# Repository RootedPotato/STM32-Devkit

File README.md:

# STM32G474CCTX Devkit

## What is it?
This is small devkit(development board) with 40 pins(2X20 Pins).
## Why I made it?
I made its for serval thinks:
- To get more knowledge about devkits
- I needed more ADC inputs than Black Pill
- Preciser PWM outputs 
- Small size factor

## Hardware
I will not name all components or all feutures with, which you can experment, but some of most important:
- Mcu: STM32G474CCTX
- Clock: 16Mhz outside clock with 2 decompling capacitors
- LDO: Its have AMS1117-3.3v, but I think that you can use others if the same footprint and same A and V
- SWO/USB: Its have SWO debuging and Micro USB B

## Pinout
### Connector J3(Left)
1. Power +3.3V
2. Power GND
3. Power VBUS
4. PC13 - TIM/GPIO
5. PC14 - GPIO
6. PC15 - GPIO
7. PA0 - ADC/TIM
8. PA1 - ADC/TIM
9. PA2 - ADC/TIM
10. PA3 - ADC/TIM
11. PA4 - ADC/TIM/SPI1
12. PA5 - ADC/TIM/SPI1
13. PA6 - ADC/TIM/SPI1
14. PA7 - ADC/TIM/SPI1
15. PB0 - ADC/TIM
16. PB1 - ADC/TIM
17. PB2 - ADC/TIM
18. PA14 - SWCLK
19. PB3 - SWO
20. PA13 - SWDIO
### Connector J6(Right)
1. Power +3.3V
2. Power GND
3. Power +5V
4. PB9 - TIM/GPIO
5. PB7 - TIM/GPIO
6. PB6 - TIM/GPIO
7. PB5 - TIM/GPIO
8. PB4 - TIM/GPIO
9. PA15 - ADC/TIM
10. PA10 - TIM/GPIO
11. PA9 - ADC/TIM
12. PA8 - ADC/TIM
13. PB15 - ADC/TIM
14. PB14 - ADC/TIM
15. PB13 - ADC/GPIO
16. PB12 - ADC/GPIO
17. PB11 - ADC/TIM
18. PB10 - TIM/GPIO
19. Power GND
20. Power +3.3V
## License
Its open source with MIT license.

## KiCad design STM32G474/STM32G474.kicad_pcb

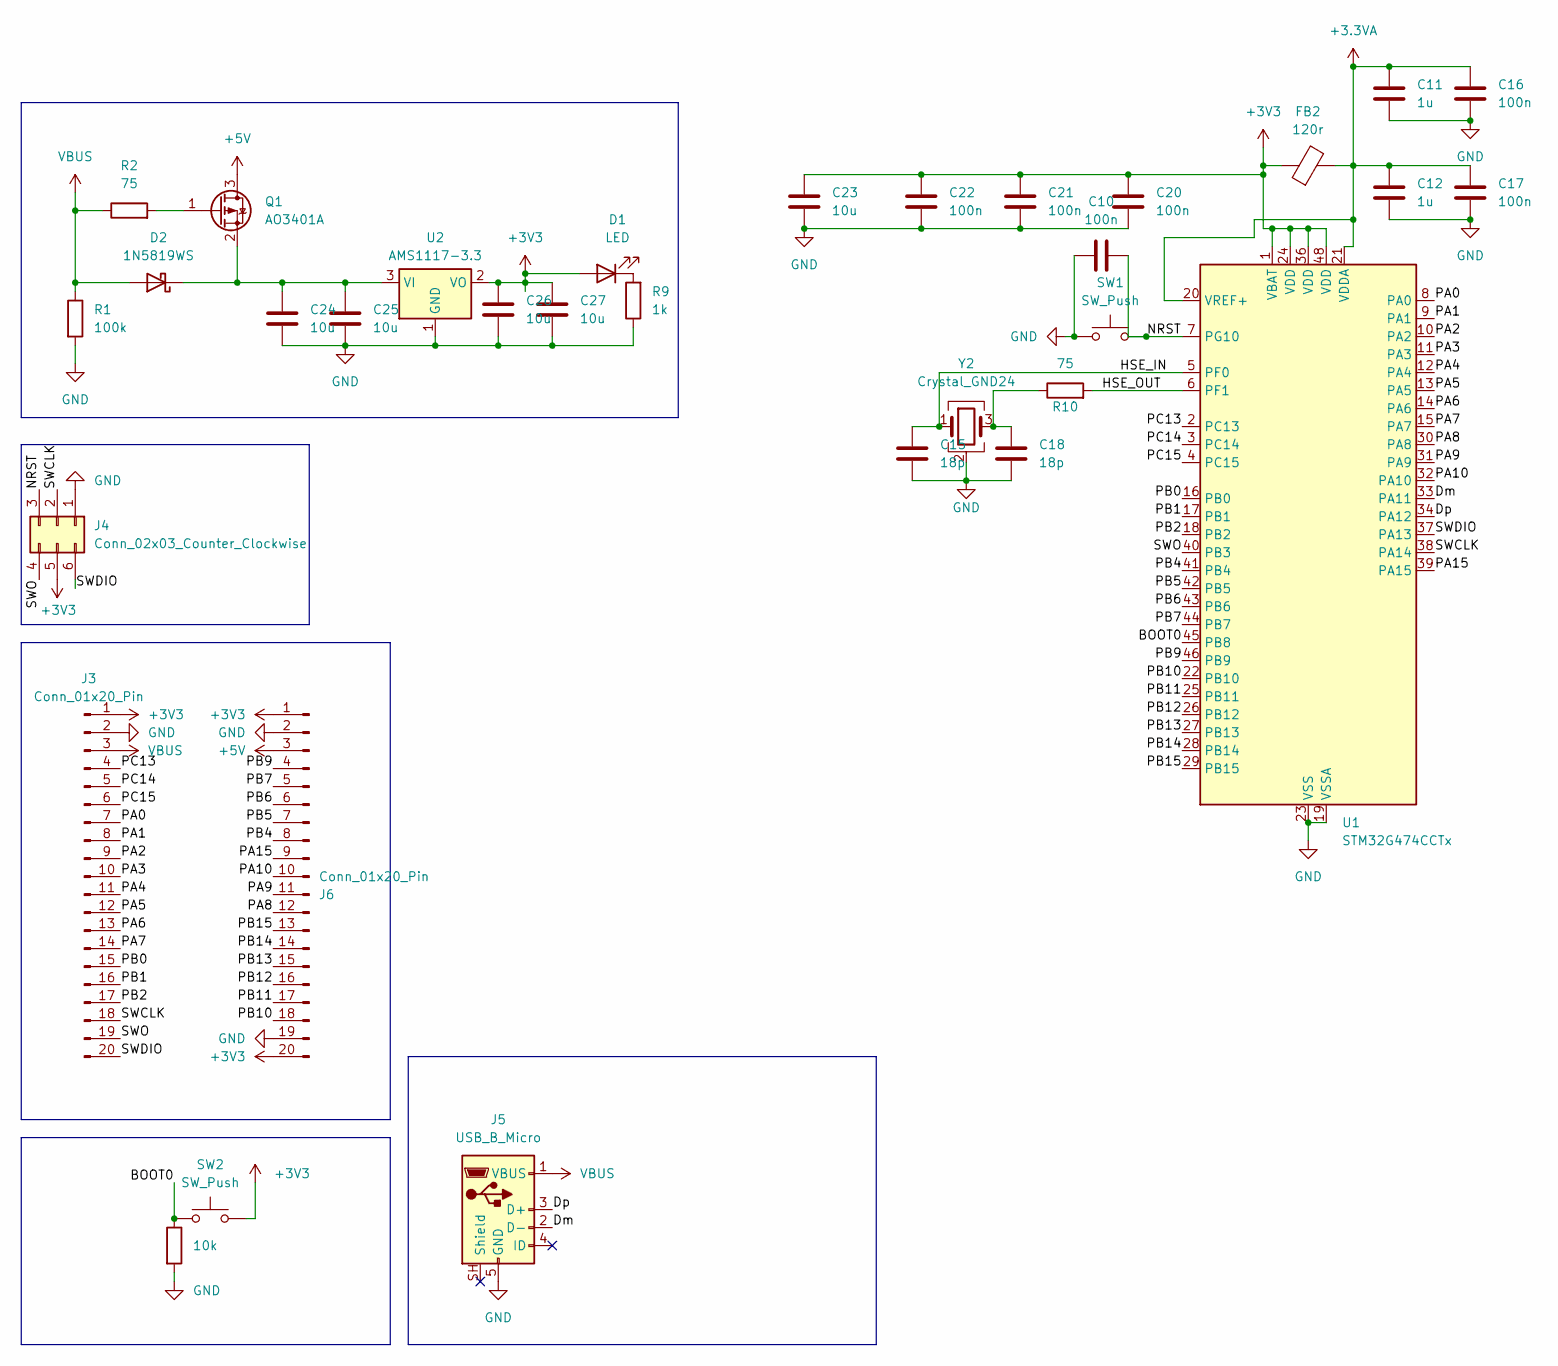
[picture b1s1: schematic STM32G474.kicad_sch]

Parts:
C10, C16, C17, C20, C21, C22: 100n; C_0805_2012Metric_Pad1.18x1.45mm_HandSolder; LCSC C49678
C11, C12: 1u; C_0805_2012Metric_Pad1.18x1.45mm_HandSolder; LCSC C15849
C15, C18: 18p; C_0805_2012Metric_Pad1.18x1.45mm_HandSolder; LCSC C113825
C23, C24, C25, C26, C27: 10u; C_0805_2012Metric_Pad1.18x1.45mm_HandSolder; LCSC C15850
D1: LED; LED_0805_2012Metric_Pad1.15x1.40mm_HandSolder; LCSC C84260
D2: 1N5819WS; D_SOD-323_HandSoldering; LCSC C191023
FB2: 120r; L_0805_2012Metric_Pad1.05x1.20mm_HandSolder; LCSC C15957
J3, J6: Conn_01x20_Pin; PinHeader_1x20_P2.54mm_Vertical
J4: Conn_02x03_Counter_Clockwise; PinSocket_2x03_P2.54mm_Vertical
J5: USB_B_Micro; USB_Micro-AB_Molex_47590-0001; LCSC C136001
Q1: AO3401A; SOT-23_Handsoldering; LCSC C347476
R1: 100k; R_0805_2012Metric_Pad1.20x1.40mm_HandSolder; LCSC C149504
R2, R10: 75; R_0805_2012Metric_Pad1.20x1.40mm_HandSolder; LCSC C2933498
R9: 1k; R_0805_2012Metric_Pad1.20x1.40mm_HandSolder; LCSC C17513
R11: 10k; R_0805_2012Metric_Pad1.20x1.40mm_HandSolder; LCSC C17414
SW1, SW2: SW_Push; SW_Push_SPST_NO_Alps_SKRK; LCSC C262416
U1: STM32G474CCTx; LQFP-48_7x7mm_P0.5mm; LCSC C730124
U2: AMS1117-3.3; SOT-223-3_TabPin2; LCSC C6186
Y2: Crystal_GND24; Crystal_SMD_3225-4Pin_3.2x2.5mm_HandSoldering; LCSC C12668

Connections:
+3.3VA: C11.1, C12.1, C16.1, C17.1, FB2.2, U1.20 (VREF+), U1.21 (VDDA)
+3V3: C20.1, C21.1, C22.1, C23.1, C26.1, C27.1, D1.2 (A), FB2.1, J3.1, J4.5, J6.1, J6.20, SW2.2, U1.1 (VBAT), U1.24 (VDD), U1.36 (VDD), U1.48 (VDD), U2.2 (VO)
+5V: J6.3, Q1.3 (D)
/<NO NET>: C15.1, U1.5 (PF0), Y2.1
/BOOT0: R11.1, SW2.1, U1.45 (PB8)
/Dm: J5.2 (D-), U1.33 (PA11)
/Dp: J5.3 (D+), U1.34 (PA12)
/HSE_OUT: R10.2, U1.6 (PF1)
/NRST: C10.2, J4.3, SW1.2, U1.7 (PG10)
/PA0: J3.7, U1.8 (PA0)
/PA1: J3.8, U1.9 (PA1)
/PA2: J3.9, U1.10 (PA2)
/PA3: J3.10, U1.11 (PA3)
/PA4: J3.11, U1.12 (PA4)
/PA5: J3.12, U1.13 (PA5)
/PA6: J3.13, U1.14 (PA6)
/PA7: J3.14, U1.15 (PA7)
/PA8: J6.12, U1.30 (PA8)
/PA9: J6.11, U1.31 (PA9)
/PA10: J6.10, U1.32 (PA10)
/PA15: J6.9, U1.39 (PA15)
/PB0: J3.15, U1.16 (PB0)
/PB1: J3.16, U1.17 (PB1)
/PB2: J3.17, U1.18 (PB2)
/PB4: J6.8, U1.41 (PB4)
/PB5: J6.7, U1.42 (PB5)
/PB6: J6.6, U1.43 (PB6)
/PB7: J6.5, U1.44 (PB7)
/PB9: J6.4, U1.46 (PB9)
/PB10: J6.18, U1.22 (PB10)
/PB11: J6.17, U1.25 (PB11)
/PB12: J6.16, U1.26 (PB12)
/PB13: J6.15, U1.27 (PB13)
/PB14: J6.14, U1.28 (PB14)
/PB15: J6.13, U1.29 (PB15)
/PC13: J3.4, U1.2 (PC13)
/PC14: J3.5, U1.3 (PC14)
/PC15: J3.6, U1.4 (PC15)
/SWCLK: J3.18, J4.2, U1.38 (PA14)
/SWDIO: J3.20, J4.6, U1.37 (PA13)
/SWO: J3.19, J4.4, U1.40 (PB3)
GND: C10.1, C11.2, C12.2, C15.2, C16.2, C17.2, C18.2, C20.2, C21.2, C22.2, C23.2, C24.2, C25.2, C26.2, C27.2, J3.2, J4.1, J5.5 (GND), J6.2, J6.19, R1.2, R9.1, R11.2, SW1.1, U1.19 (VSSA), U1.23 (VSS), U1.35 (VSS), U1.47 (VSS), U2.1 (GND), Y2.2 (G), Y2.4 (G)
unnamed: C18.1, R10.1, Y2.3
unnamed: D1.1 (K), R9.2
unnamed: C24.1, C25.1, D2.1 (K), Q1.2 (S), U2.3 (VI)
unnamed: Q1.1 (G), R2.2
VBUS: D2.2 (A), J3.3, J5.1 (VBUS), R1.1, R2.1

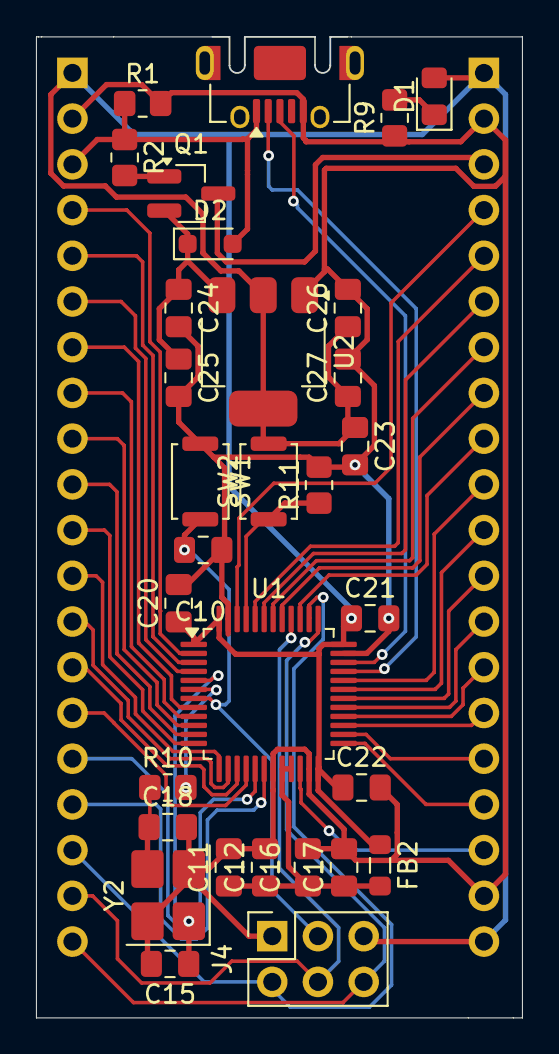
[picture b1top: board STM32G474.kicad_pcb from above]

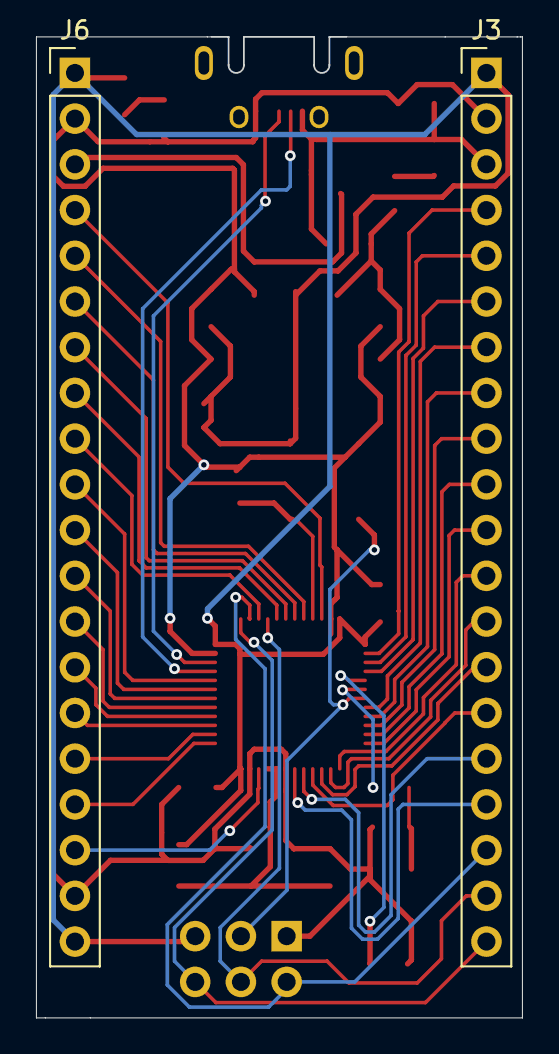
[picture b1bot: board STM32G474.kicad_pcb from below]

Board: 2 copper layers, 27.0 x 54.5 mm, 33 parts (2 on the bottom side), 47 nets.

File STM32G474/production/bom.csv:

Designator,Footprint,Quantity,Value,LCSC Part #
"C10, C16, C17, C20, C21, C22",0805,6,100n,C49678
"C11, C12",0805,2,1u,C15849
"C15, C18",0805,2,18p,C113825
"C23, C24, C25, C26, C27",0805,5,10u,C15850
D1,0805,1,LED,C84260
D2,D_SOD-323_HandSoldering,1,1N5819WS,C191023
FB2,0805,1,120r,C15957
"J3, J6",PinHeader_1x20_P2.54mm_Vertical,2,Conn_01x20_Pin,
J4,PinSocket_2x03_P2.54mm_Vertical,1,Conn_02x03_Counter_Clockwise,
J5,USB_Micro-AB_Molex_47590-0001,1,USB_B_Micro,C136001
Q1,SOT-23_Handsoldering,1,AO3401A,C347476
R1,0805,1,100k,C149504
"R10, R2",0805,2,75,C2933498
R11,0805,1,10k,C17414
R9,0805,1,1k,C17513
"SW1, SW2",SW_Push_SPST_NO_Alps_SKRK,2,SW_Push,C262416
U1,LQFP-48_7x7mm_P0.5mm,1,STM32G474CCTx,C730124
U2,SOT-223-3_TabPin2,1,AMS1117-3.3,C6186
Y2,Crystal_SMD_3225-4Pin_3.2x2.5mm_HandSoldering,1,Crystal_GND24,C12668

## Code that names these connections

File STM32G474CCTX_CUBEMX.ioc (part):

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Mcu.Name=STM32G474C(B-C-E)Tx
Mcu.Package=LQFP48
Mcu.UserName=STM32G474CCTx
PA11.Mode=Device
PA11.Signal=USB_DM
PA12.Mode=Device
PA12.Signal=USB_DP
PA13.Mode=Trace_Asynchronous_SW
PA13.Signal=SYS_JTMS-SWDIO
PA14.Mode=Trace_Asynchronous_SW
PA14.Signal=SYS_JTCK-SWCLK
PB3.Mode=Trace_Asynchronous_SW
PB3.Signal=SYS_JTDO-SWO
PF0-OSC_IN.Mode=HSE-External-Oscillator
PF0-OSC_IN.Signal=RCC_OSC_IN
PF1-OSC_OUT.Mode=HSE-External-Oscillator
PF1-OSC_OUT.Signal=RCC_OSC_OUT
RCC.HSE_VALUE=8000000
RCC.SYSCLKFreq_VALUE=168000000
RCC.SYSCLKSource=RCC_SYSCLKSOURCE_PLLCLK
board=custom
